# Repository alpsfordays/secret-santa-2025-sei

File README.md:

# Secret Santa 2025 : Sei
This repo holds all the files for my secret santa gift, *La Carte Blanche*; a card-sized 14-key keyboard with PG1316S and M switches running FAK on a CH552T.

## PCB
All the PCB files and [gerbers](pcb/secret-santa-2025/jlcpcb/gerber/) are available; the PCB can be assembled with 14 0805 1N4148 diodes, 2 0605 100nF capacitors, 2 0605 5.1K resistors and a CH55T. You will need 9 PG1316S and 5 PG1316M switches.
For the min-spec USB-C connector, I recommend having the PCB made with ENIG plating to increase durability. It will need to be 0.8mm thick (0.6mm works too but would be a little loose). 
The reset button is available [here](https://www.lcsc.com/product-detail/C963197.html) from LCSC.

## Firmware
Put the [carte-blanche](firmware/carte-blanche/) folder into the keyboards folder of your fak-config and compile.  The [.ihx](firmware/carte-blanche.ihx) is also included if you would like to test your PCB; the base layout is alphabetical from left to right, top down.

## Credits and Licensing
Credit to [AnasMalas](https://github.com/AnasMalas/pcb-edge-usb-c) for the min-spec USB-C connector. The silk was drawn by me with technical drawings created from STEP files made available by Kailh.
The USB-C connector is under a CC-1.0 licence, and the project proper is under the [CERN-OHL-S-2.0 licence](LICENSE).

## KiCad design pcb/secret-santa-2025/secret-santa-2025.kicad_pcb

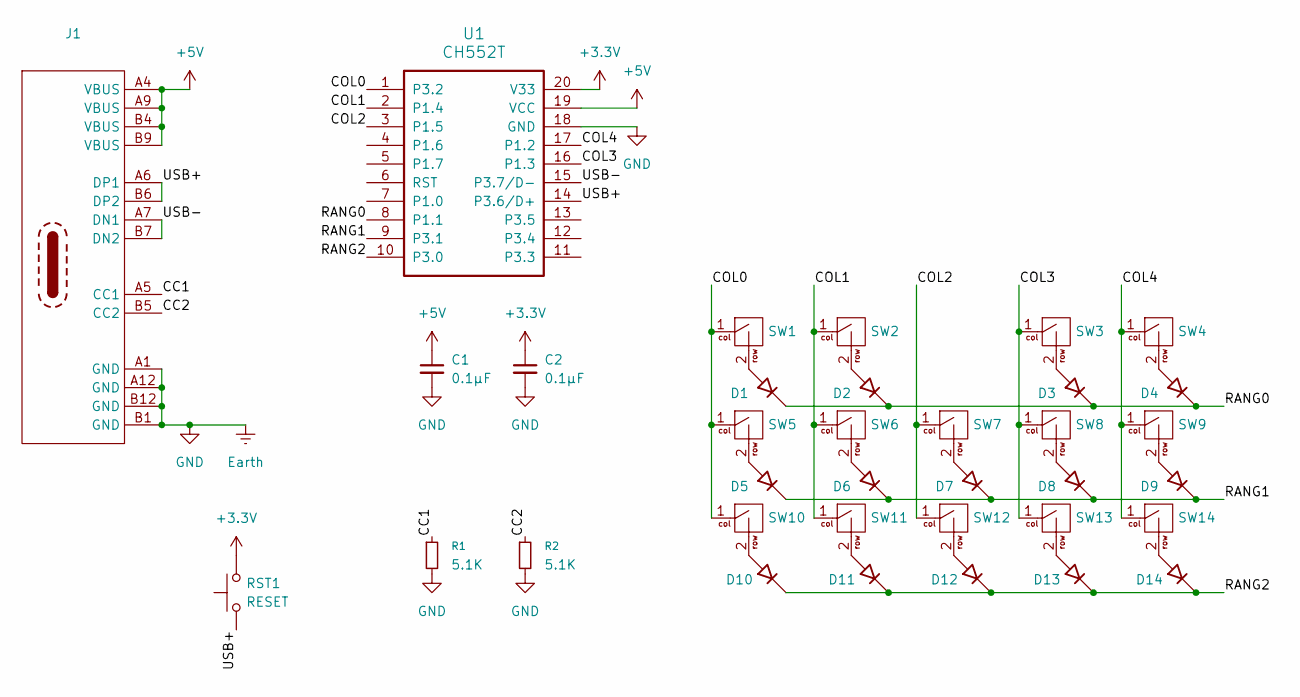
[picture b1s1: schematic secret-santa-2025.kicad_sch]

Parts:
C1, C2: 0.1µF; C_0603_1608Metric
D1, D2, D3, D4, D5, D6, D7, D8, D9, D10, D11, D12, D13, D14: D_45deg; D_0805_2012Metric
J1: PCBTypeC_14P
R1, R2: 5.1K; C_0603_1608Metric
RST1: RESET; GT-TC024
SW1, SW2, SW3, SW4, SW5, SW6, SW7, SW8, SW9: PG1316S_1U_castellated
SW10, SW11, SW12, SW13, SW14: PG1316M_0.7U_castellated
U1: CH552T; TSSOP-20_4.4x6.5mm_P0.65mm

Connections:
+3.3V: C2.1, RST1.2, U1.20 (V33)
+5V: C1.1, J1.A4 (VBUS), J1.A9 (VBUS), J1.B4 (VBUS), J1.B9 (VBUS), U1.19 (VCC)
/CC1: J1.A5 (CC1), R1.1
/CC2: J1.B5 (CC2), R2.1
/COL0: SW1.1, SW5.1, SW10.1, U1.1 (P3.2)
/COL1: SW2.1, SW6.1, SW11.1, U1.2 (P1.4)
/COL2: SW7.1, SW12.1, U1.3 (P1.5)
/COL3: SW3.1, SW8.1, SW13.1, U1.16 (P1.3)
/COL4: SW4.1, SW9.1, SW14.1, U1.17 (P1.2)
/RANG0: D1.1 (K), D2.1 (K), D3.1 (K), D4.1 (K), U1.8 (P1.1)
/RANG1: D5.1 (K), D6.1 (K), D7.1 (K), D8.1 (K), D9.1 (K), U1.9 (P3.1)
/RANG2: D10.1 (K), D11.1 (K), D12.1 (K), D13.1 (K), D14.1 (K), U1.10 (P3.0)
/USB+: J1.A6 (DP1), J1.B6 (DP2), RST1.1, U1.14 (P3.6/D+)
/USB-: J1.A7 (DN1), J1.B7 (DN2), U1.15 (P3.7/D-)
Earth: C1.2, C2.2, J1.A1 (GND), J1.A12 (GND), J1.B1 (GND), J1.B12 (GND), R1.2, R2.2, U1.18 (GND)
unnamed: D1.2 (A), SW1.2
unnamed: D2.2 (A), SW2.2
unnamed: D3.2 (A), SW3.2
unnamed: D4.2 (A), SW4.2
unnamed: D5.2 (A), SW5.2
unnamed: D6.2 (A), SW6.2
unnamed: D7.2 (A), SW7.2
unnamed: D8.2 (A), SW8.2
unnamed: D9.2 (A), SW9.2
unnamed: D10.2 (A), SW10.2
unnamed: D11.2 (A), SW11.2
unnamed: D12.2 (A), SW12.2
unnamed: D13.2 (A), SW13.2
unnamed: D14.2 (A), SW14.2

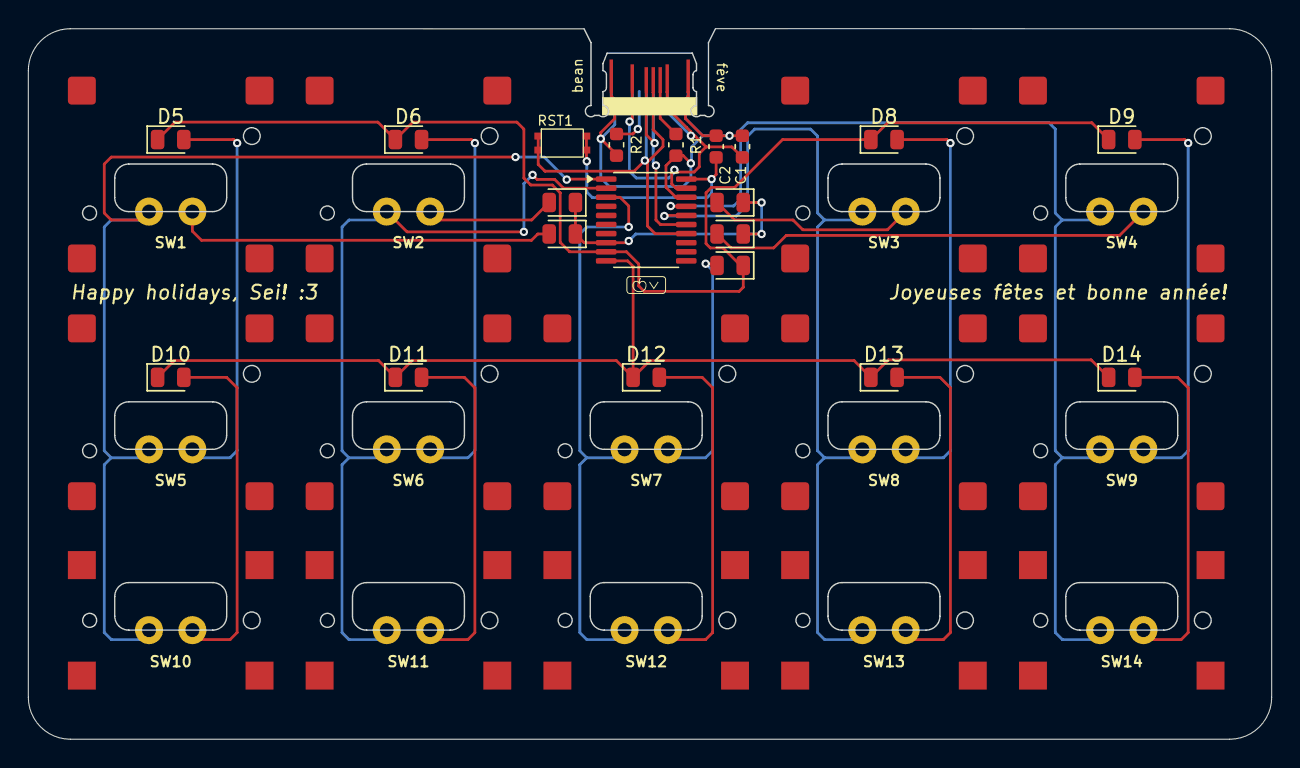
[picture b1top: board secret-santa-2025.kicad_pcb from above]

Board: 2 copper layers, 88.8 x 50.8 mm, 35 parts (0 on the bottom side), 29 nets.

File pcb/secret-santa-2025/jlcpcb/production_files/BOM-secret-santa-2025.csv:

Comment,Designator,Footprint,LCSC,Quantity
D_45deg,D6,D_0805_2012Metric,,1
~,SW13,PG1316M_0.7U_castellated,,1
~,SW11,PG1316M_0.7U_castellated,,1
D_45deg,D10,D_0805_2012Metric,,1
D_45deg,D7,D_0805_2012Metric,,1
~,SW2,PG1316S_1U_castellated,,1
~,SW5,PG1316S_1U_castellated,,1
D_45deg,D5,D_0805_2012Metric,,1
D_45deg,D4,D_0805_2012Metric,,1
~,SW4,PG1316S_1U_castellated,,1
D_45deg,D9,D_0805_2012Metric,,1
D_45deg,D1,D_0805_2012Metric,,1
D_45deg,D13,D_0805_2012Metric,,1
D_45deg,D2,D_0805_2012Metric,,1
0.1µF,C2,C_0603_1608Metric,,1
RESET,RST1,GT-TC024,,1
D_45deg,D3,D_0805_2012Metric,,1
5.1K,R2,C_0603_1608Metric,,1
~,SW10,PG1316M_0.7U_castellated,,1
D_45deg,D14,D_0805_2012Metric,,1
D_45deg,D8,D_0805_2012Metric,,1
5.1K,R1,C_0603_1608Metric,,1
~,SW1,PG1316S_1U_castellated,,1
D_45deg,D11,D_0805_2012Metric,,1
~,SW14,PG1316M_0.7U_castellated,,1
D_45deg,D12,D_0805_2012Metric,,1
~,SW6,PG1316S_1U_castellated,,1
~,SW9,PG1316S_1U_castellated,,1
~,SW7,PG1316S_1U_castellated,,1
~,SW3,PG1316S_1U_castellated,,1
0.1µF,C1,C_0603_1608Metric,,1
CH552T,U1,TSSOP-20_4.4x6.5mm_P0.65mm,,1
~,SW8,PG1316S_1U_castellated,,1
~,SW12,PG1316M_0.7U_castellated,,1

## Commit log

2025-12-25 Fix credits in README.md
